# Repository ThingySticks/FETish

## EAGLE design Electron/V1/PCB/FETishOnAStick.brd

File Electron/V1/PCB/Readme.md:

FETish On A Stick
=================

Triple FET on a Stick.

2 x large high current FETS
1 x low current (max 200mA) FET

All FET's PWM-able (see notes)

Notes:
------

V1.00 - Track missing from A4, needs A4 outer pad soldered to Socket

A4 and D3 share PWM channel. 
* Use digitalWrite with one and PWM with the other
* or digitalWrite with both
* Do not use PWM with both (or they will both have the same PWM value).

TODO: 
-----
* Connect A4 properly
* Perhaps have option of A4 OR WKP to allow for all 3 FETs to be used at once.
* Increase font size for Photon/Electron markers

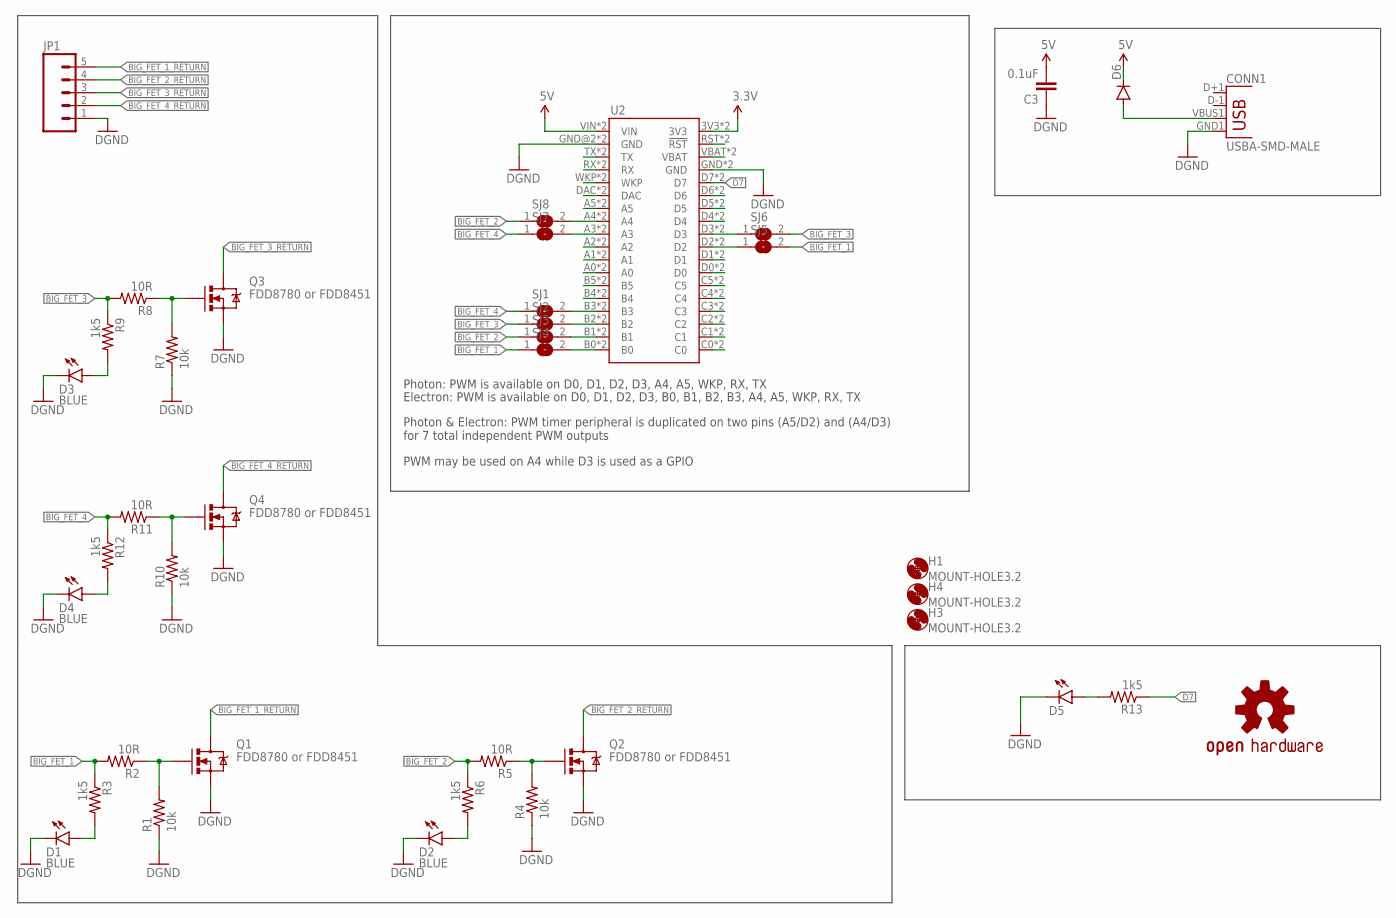
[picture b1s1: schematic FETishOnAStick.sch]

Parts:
C3: 0.1uF; 0805
CONN1: USBA-SMD-MALE; USB-A-SMT-MALE
D1, D2, D3, D4: BLUE; LED-1206
D5: LED1206-BOTTOM; LED-1206-BOTTOM
D6: DIODESMA; SMA-DIODE
H1, H3, H4: MOUNT-HOLE3.2; 3,2
JP1: M05SCREW; SCREWTERMINAL-3.5MM-5
LOGO1: OSHW-LOGOM; OSHW-LOGO-M
Q1, Q2, Q3, Q4: FDD8780 or FDD8451; DPAK
R1, R4, R7, R10: 10k; 0805
R2, R5, R8, R11: 10R; 0805
R3, R6, R9, R12, R13: 1k5; 0805
SJ1, SJ2, SJ3, SJ4, SJ5, SJ6, SJ7, SJ8: SJ
U2: ELECTRONDUALNAMED; ELECTRON_SIMPLE_SILK_NAMES_DUAL

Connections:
3.3V: U2.3V3, U2.3V3_1 (3V3)
5V: C3.2, D6.C, U2.VIN, U2.VIN_1B (VIN)
BIG_FET_1: R2.2, R3.1, SJ4.1, SJ5.2
BIG_FET_1_RETURN: JP1.5, Q1.4 (D)
BIG_FET_2: R5.2, R6.1, SJ3.1, SJ8.1
BIG_FET_2_RETURN: JP1.4, Q2.4 (D)
BIG_FET_3: R8.2, R9.1, SJ2.1, SJ6.2
BIG_FET_3_RETURN: JP1.3, Q3.4 (D)
BIG_FET_4: R11.2, R12.1, SJ1.1, SJ7.1
BIG_FET_4_RETURN: JP1.2, Q4.4 (D)
D7: R13.1, U2.D7, U2.D7_1 (D7)
GND: C3.1, CONN1.GND1 (GND), D1.C, D2.C, D3.C, D4.C, D5.C, JP1.1, Q1.3 (S), Q2.3 (S), Q3.3 (S), Q4.3 (S), R1.1, R4.1, R7.1, R10.1, U2.GND, U2.GND@2 (GND), U2.GND_1 (GND), U2.GND_1B (GND)
unnamed: CONN1.VBUS1 (VBUS), D6.A
unnamed: Q4.1 (G), R10.2, R11.1
unnamed: U2.VBAT, U2.VBATT_1 (VBAT)
unnamed: U2.RST (!RST), U2.RST_1 (!RST)
unnamed: D1.A, R3.2
unnamed: D2.A, R6.2
unnamed: D4.A, R12.2
unnamed: U2.D6, U2.D6_1 (D6)
unnamed: U2.D5, U2.D5_1 (D5)
unnamed: D5.A, R13.2
unnamed: U2.D4, U2.D4_1 (D4)
unnamed: Q3.1 (G), R7.2, R8.1
unnamed: D3.A, R9.2
unnamed: U2.C5, U2.C5_1 (C5)
unnamed: U2.C4, U2.C4_1 (C4)
unnamed: U2.C3, U2.C3_1 (C3)
unnamed: U2.C2, U2.C2_1 (C2)
unnamed: Q1.1 (G), R1.2, R2.1
unnamed: U2.C1, U2.C1_1 (C1)
unnamed: U2.C0, U2.C0_1 (C0)
unnamed: SJ8.2, U2.A4, U2.A4_1 (A4)
unnamed: SJ4.2, U2.B0, U2.B0_1 (B0)
unnamed: SJ3.2, U2.B1, U2.B1_1 (B1)
unnamed: SJ2.2, U2.B2, U2.B2_1 (B2)
unnamed: SJ1.2, U2.B3, U2.B3_1 (B3)
unnamed: U2.B4, U2.B4_1 (B4)
unnamed: U2.B5, U2.B5_1 (B5)
unnamed: U2.A0, U2.A0_1 (A0)
unnamed: U2.A1, U2.A1_1 (A1)
unnamed: U2.A2, U2.A2_1 (A2)
unnamed: SJ7.2, U2.A3, U2.A3_1 (A3)
unnamed: SJ6.1, U2.D3, U2.D3_1 (D3)
unnamed: U2.A5, U2.A5_1 (A5)
unnamed: U2.DAC, U2.DAC_1 (DAC)
unnamed: U2.WKP, U2.WKP_1 (WKP)
unnamed: U2.RX, U2.RX_1 (RX)
unnamed: U2.TX, U2.TX_1 (TX)
unnamed: SJ5.1, U2.D2, U2.D2_1 (D2)
unnamed: Q2.1 (G), R4.2, R5.1
SCL: U2.D1, U2.D1_1 (D1)
SDA: U2.D0, U2.D0_1 (D0)

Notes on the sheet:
Photon: PWM is available on D0, D1, D2, D3, A4, A5, WKP, RX, TX
Photon & Electron: PWM timer peripheral is duplicated on two pins (A5/D2) and (A4/D3) for 7 total independent PWM outputs
Electron: PWM is available on D0, D1, D2, D3, B0, B1, B2, B3, A4, A5, WKP, RX, TX
PWM may be used on A4 while D3 is used as a GPIO

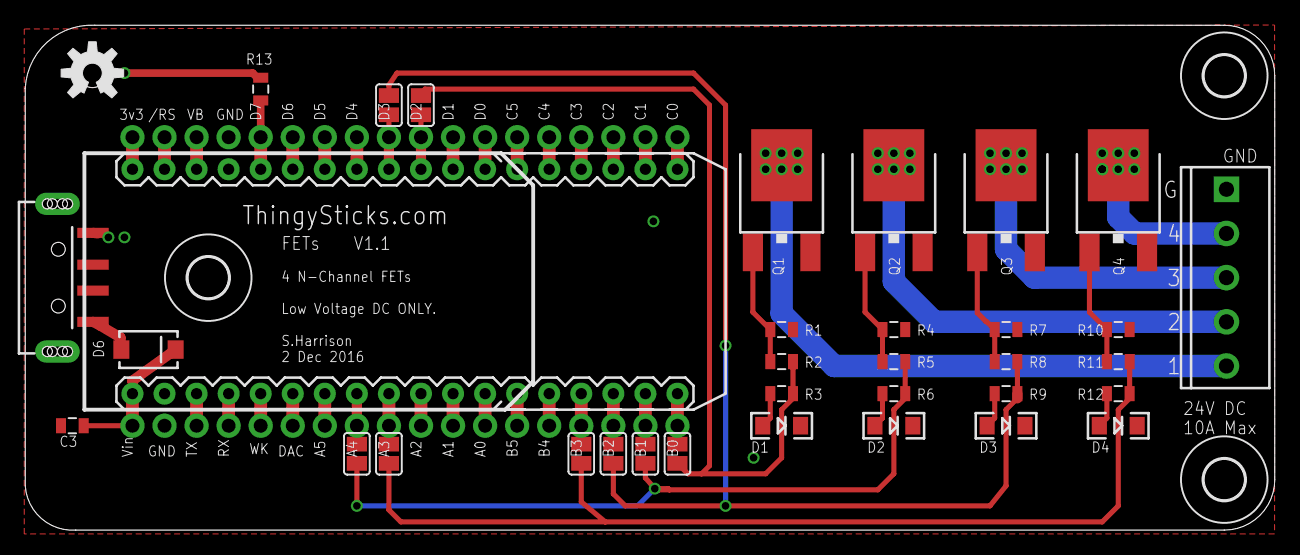
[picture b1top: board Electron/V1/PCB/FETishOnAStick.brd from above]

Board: 2 copper layers, 99.0 x 40.0 mm, 39 parts (1 on the bottom side), 53 nets.

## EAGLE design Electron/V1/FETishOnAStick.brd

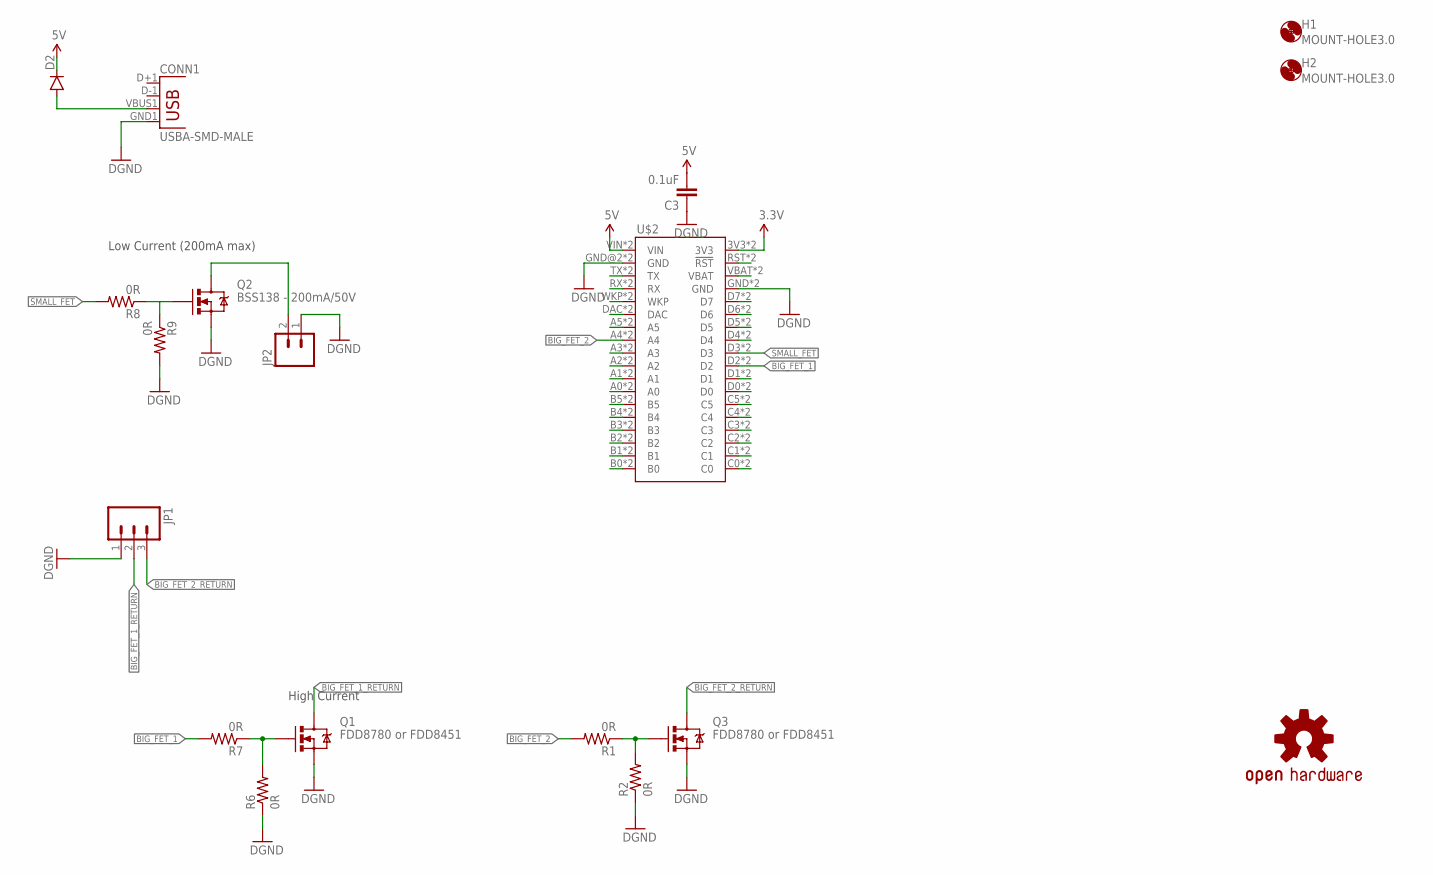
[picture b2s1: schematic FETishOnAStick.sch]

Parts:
C3: 0.1uF; 0805
CONN1: USBA-SMD-MALE; USB-A-SMT-MALE
D2: DIODESMA; SMA-DIODE
H1, H2: MOUNT-HOLE3.0; 3,0
JP1: M03-SCREW-5MM; SCREWTERMINAL-5MM-3
JP2: M02POLAR; MOLEX-1X2
LOGO2: OSHW-LOGOS; OSHW-LOGO-S
Q1, Q3: FDD8780 or FDD8451; DPAK
Q2: BSS138 - 200mA/50V; SOT23-3
R1, R2, R6, R7, R8, R9: 0R; 0805
U$2: ELECTRONDUALNAMED; ELECTRON_SIMPLE_SILK_NAMES_DUAL

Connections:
3.3V: U$2.3V3, U$2.3V3_1 (3V3)
5V: C3.2, D2.C, U$2.VIN, U$2.VIN_1B (VIN)
BIG_FET_1: R7.2, U$2.D2, U$2.D2_1 (D2)
BIG_FET_1_RETURN: JP1.2, Q1.4 (D)
BIG_FET_2: R1.2, U$2.A4, U$2.A4_1 (A4)
BIG_FET_2_RETURN: JP1.3, Q3.4 (D)
GND: C3.1, CONN1.GND1 (GND), JP1.1, JP2.1, Q1.3 (S), Q2.2 (S), Q3.3 (S), R2.1, R6.1, R9.2, U$2.GND, U$2.GND@2 (GND), U$2.GND_1 (GND), U$2.GND_1B (GND)
unnamed: CONN1.VBUS1 (VBUS), D2.A
unnamed: Q3.1 (G), R1.1, R2.2
unnamed: U$2.VBAT, U$2.VBATT_1 (VBAT)
unnamed: U$2.RST (!RST), U$2.RST_1 (!RST)
unnamed: U$2.D7, U$2.D7_1 (D7)
unnamed: Q2.1 (G), R8.1, R9.1
unnamed: U$2.D6, U$2.D6_1 (D6)
unnamed: U$2.D5, U$2.D5_1 (D5)
unnamed: U$2.D4, U$2.D4_1 (D4)
unnamed: U$2.C5, U$2.C5_1 (C5)
unnamed: U$2.C4, U$2.C4_1 (C4)
unnamed: U$2.C3, U$2.C3_1 (C3)
unnamed: U$2.C2, U$2.C2_1 (C2)
unnamed: Q1.1 (G), R6.2, R7.1
unnamed: U$2.C1, U$2.C1_1 (C1)
unnamed: U$2.C0, U$2.C0_1 (C0)
unnamed: U$2.B0, U$2.B0_1 (B0)
unnamed: U$2.B1, U$2.B1_1 (B1)
unnamed: U$2.B2, U$2.B2_1 (B2)
unnamed: U$2.B3, U$2.B3_1 (B3)
unnamed: U$2.B4, U$2.B4_1 (B4)
unnamed: U$2.B5, U$2.B5_1 (B5)
unnamed: U$2.A0, U$2.A0_1 (A0)
unnamed: U$2.A1, U$2.A1_1 (A1)
unnamed: U$2.A2, U$2.A2_1 (A2)
unnamed: U$2.A3, U$2.A3_1 (A3)
unnamed: U$2.A5, U$2.A5_1 (A5)
unnamed: U$2.DAC, U$2.DAC_1 (DAC)
unnamed: U$2.WKP, U$2.WKP_1 (WKP)
unnamed: U$2.RX, U$2.RX_1 (RX)
unnamed: U$2.TX, U$2.TX_1 (TX)
SCL: U$2.D1, U$2.D1_1 (D1)
SDA: U$2.D0, U$2.D0_1 (D0)
SMALL_FET: R8.2, U$2.D3, U$2.D3_1 (D3)
SMALL_FET_RETURN: JP2.2, Q2.3 (D)

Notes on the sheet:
High Current
Low Current (200mA max)

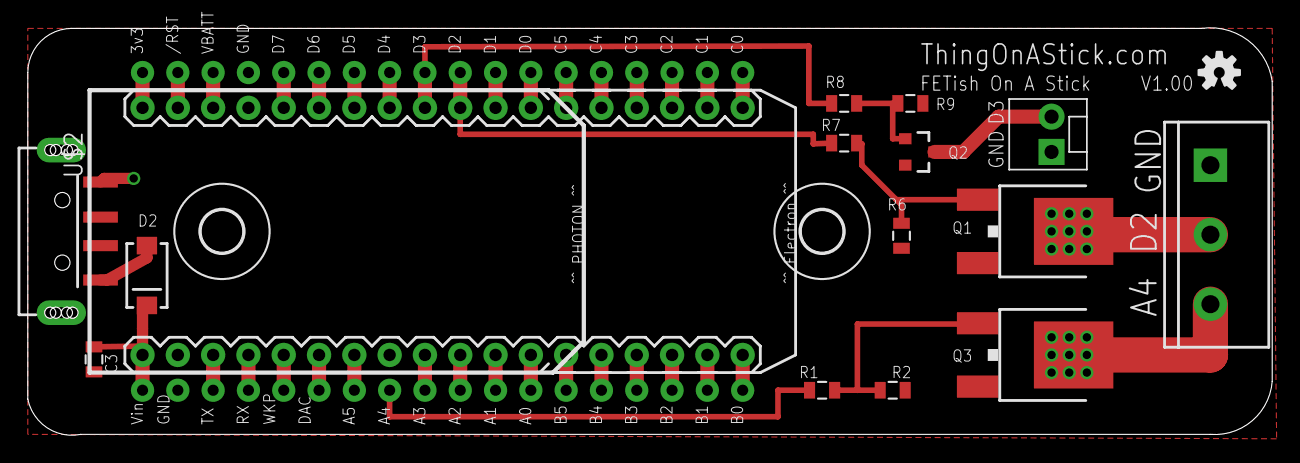
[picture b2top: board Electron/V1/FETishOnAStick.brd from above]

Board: 2 copper layers, 89.5 x 29.3 mm, 18 parts (0 on the bottom side), 42 nets.

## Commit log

2016-02-06 Initial version
2016-02-06 Moved OSH logo
2016-02-22 Initial version.
    NB: Missing track for A4.
2016-12-22 Updated identifiers, tidied up and added BOMs and images
2017-01-04 Fixed BOM validation issues.
2017-01-05 Tidied up schematic.
    Added sample code.

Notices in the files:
parts and their libraries:
SparkFun-Connectors: Licensing: Creative Commons ShareAlike 4.0 International - https://creativecommons.org/licenses/by-sa/4.0
